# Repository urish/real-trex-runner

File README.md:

# In-Real-Life TRex Runner

## Documentation

- [About The Project + Hardware Guide](https://medium.com/@urish/i-saw-a-dinosaur-or-how-i-built-a-real-life-version-of-chrome-t-rex-game-92175f6cad2c)
- [Software Guide](https://www.javascriptjanuary.com/blog/irl-offline-t-rex-game-powered-by-javascript)

## License

[CC-BY-SA](https://creativecommons.org/licenses/by-sa/4.0/)

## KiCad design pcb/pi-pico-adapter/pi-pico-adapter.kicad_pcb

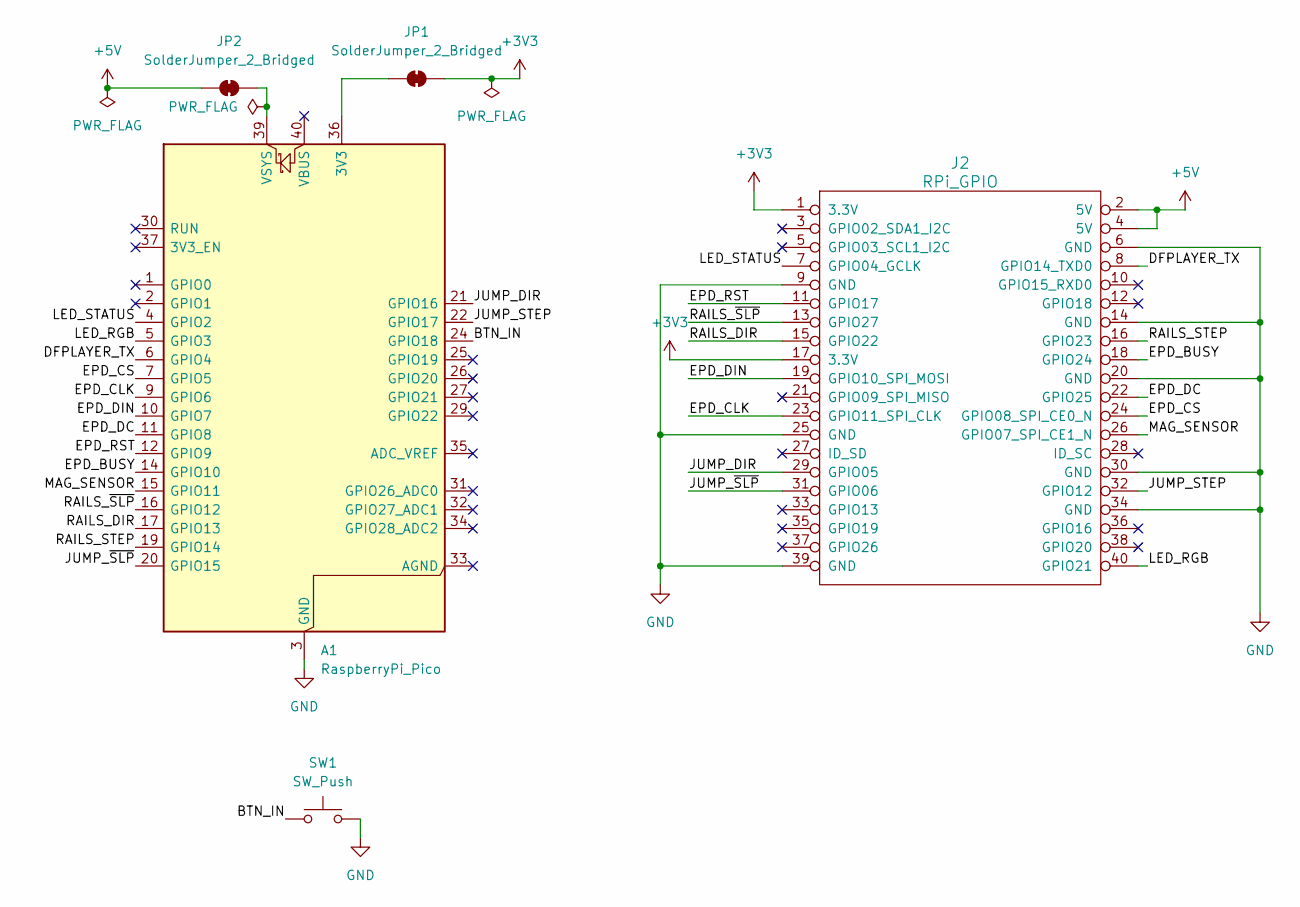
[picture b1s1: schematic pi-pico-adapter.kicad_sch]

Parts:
A1: RaspberryPi_Pico; RaspberryPi_Pico_Common_Unspecified
J2: RPi_GPIO; PinHeader_2x20_P2.54mm_Vertical
JP1, JP2: SolderJumper_2_Bridged; SolderJumper-2_P1.3mm_Bridged_RoundedPad1.0x1.5mm
SW1: SW_Push; PinHeader_1x02_P2.54mm_Vertical

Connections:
+3V3: J2.1 (3.3V), J2.17 (3.3V), JP1.2 (B)
+5V: J2.2 (5V), J2.4 (5V), JP2.1 (A)
/BTN_IN: A1.24 (GPIO18), SW1.1
/DFPLAYER_TX: A1.6 (GPIO4), J2.8 (GPIO14_TXD0)
/EPD_BUSY: A1.14 (GPIO10), J2.18 (GPIO24)
/EPD_CLK: A1.9 (GPIO6), J2.23 (GPIO11_SPI_CLK)
/EPD_CS: A1.7 (GPIO5), J2.24 (GPIO08_SPI_CE0_N)
/EPD_DC: A1.11 (GPIO8), J2.22 (GPIO25)
/EPD_DIN: A1.10 (GPIO7), J2.19 (GPIO10_SPI_MOSI)
/EPD_RST: A1.12 (GPIO9), J2.11 (GPIO17)
/JUMP_DIR: A1.21 (GPIO16), J2.29 (GPIO05)
/JUMP_STEP: A1.22 (GPIO17), J2.32 (GPIO12)
/JUMP_~SLP: A1.20 (GPIO15), J2.31 (GPIO06)
/LED_RGB: A1.5 (GPIO3), J2.40 (GPIO21)
/LED_STATUS: A1.4 (GPIO2), J2.7 (GPIO04_GCLK)
/MAG_SENSOR: A1.15 (GPIO11), J2.26 (GPIO07_SPI_CE1_N)
/RAILS_DIR: A1.17 (GPIO13), J2.15 (GPIO22)
/RAILS_STEP: A1.19 (GPIO14), J2.16 (GPIO23)
/RAILS_~SLP: A1.16 (GPIO12), J2.13 (GPIO27)
GND: A1.3 (GND), A1.8 (GND), A1.13 (GND), A1.18 (GND), A1.23 (GND), A1.28 (GND), A1.38 (GND), J2.6 (GND), J2.9 (GND), J2.14 (GND), J2.20 (GND), J2.25 (GND), J2.30 (GND), J2.34 (GND), J2.39 (GND), SW1.2
unnamed: A1.36 (3V3), JP1.1 (A)
unnamed: A1.39 (VSYS), JP2.2 (B)

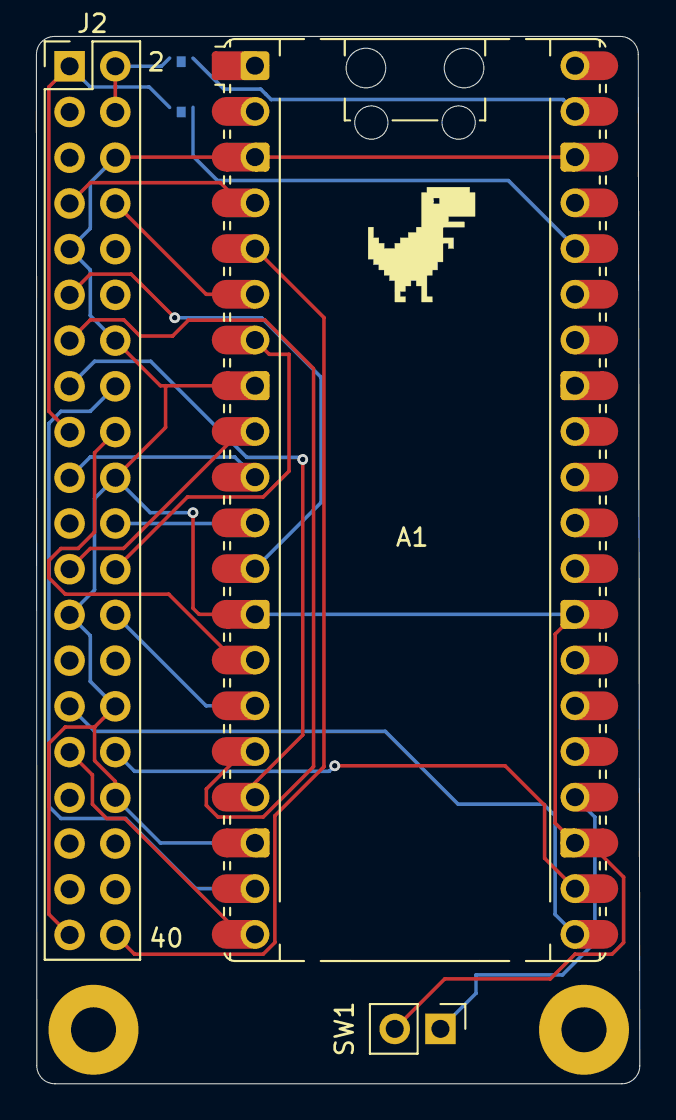
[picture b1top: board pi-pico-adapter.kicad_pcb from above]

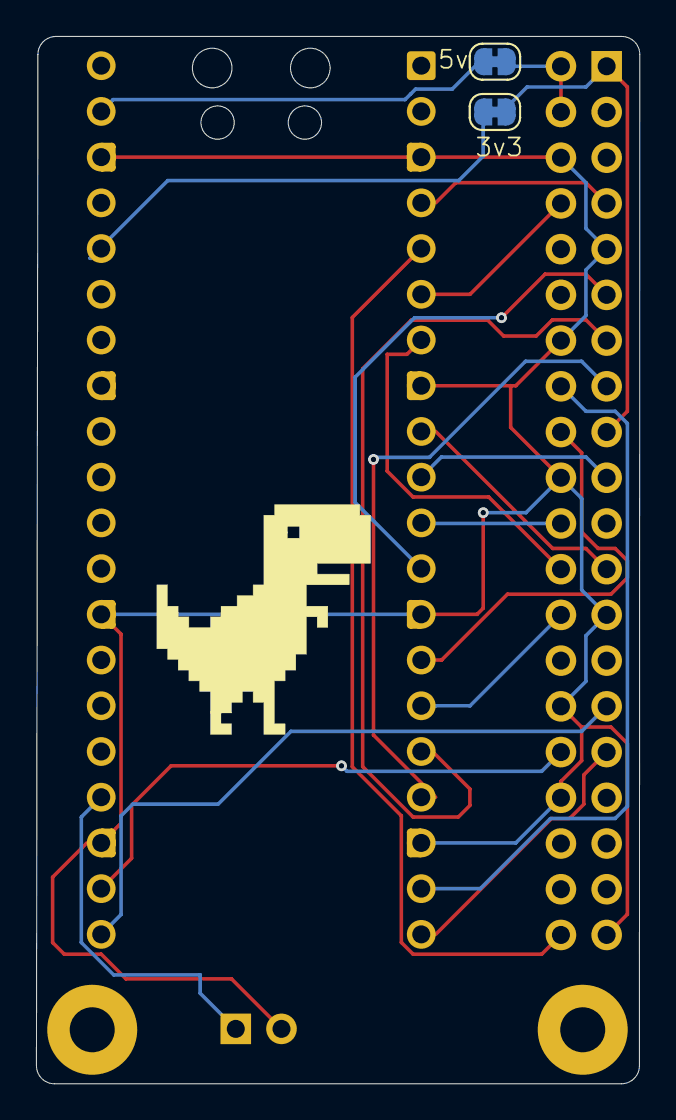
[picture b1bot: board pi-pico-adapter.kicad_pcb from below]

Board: 2 copper layers, 33.5 x 58.2 mm, 7 parts (3 on the bottom side), 22 nets.

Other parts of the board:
TREX1: trex
TREX2: trex-big

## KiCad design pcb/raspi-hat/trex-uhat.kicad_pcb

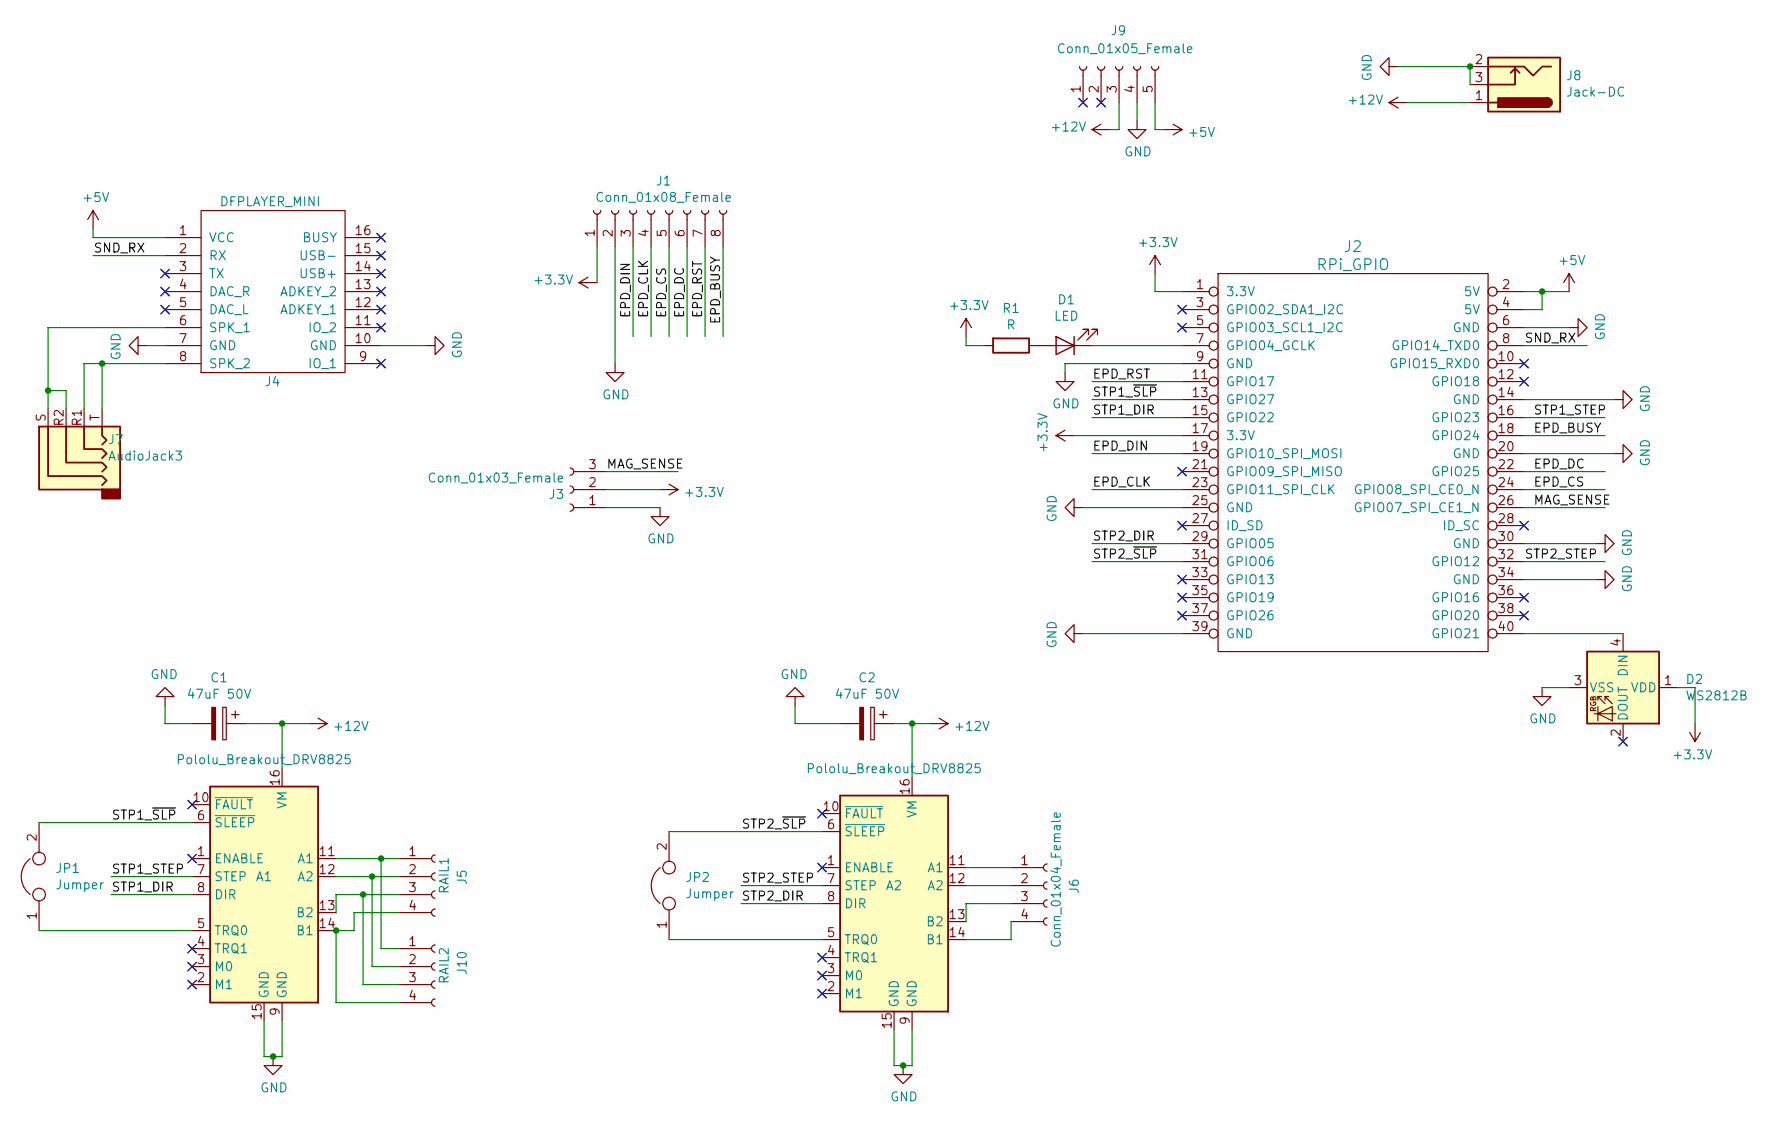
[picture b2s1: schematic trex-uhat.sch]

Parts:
A1, A2: Pololu_Breakout_DRV8825; Pololu_Breakout-16_15.2x20.3mm
C1, C2: 47uF 50V; CP_Radial_D6.3mm_P2.50mm
D1: LED; LED_D3.0mm
D2: WS2812B; LED_WS2812B_PLCC4_5.0x5.0mm_P3.2mm
J1: Conn_01x08_Female; PinSocket_1x08_P2.54mm_Vertical
J2: RPi_GPIO; PinSocket_2x20_P2.54mm_Vertical
J3: Conn_01x03_Female; PinSocket_1x03_P2.54mm_Vertical
J4: DFPLAYER_MINI; DFPlayer_Mini
J5: RAIL1; PinSocket_1x04_P2.54mm_Vertical
J6: Conn_01x04_Female; PinSocket_1x04_P2.54mm_Vertical
J7: AudioJack3; Jack_3.5mm_PJ320E_Horizontal
J8: Jack-DC; BarrelJack_CUI_PJ-102AH_Horizontal
J9: Conn_01x05_Female; PinSocket_1x05_P2.54mm_Vertical
J10: RAIL2; PinSocket_1x04_P2.54mm_Vertical
JP1, JP2: Jumper; SolderJumper-2_P1.3mm_Bridged_RoundedPad1.0x1.5mm
R1: R; R_1206_3216Metric

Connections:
+3V3: D2.1 (VDD), J1.1, J2.1 (3.3V), J2.17 (3.3V), J3.2, R1.2
+5V: J2.2 (5V), J2.4 (5V), J4.1 (VCC), J9.5
+12V: A1.16 (VM), A2.16 (VM), C1.1, C2.1, J8.1, J9.3
/EPD_BUSY: J1.8, J2.18 (GPIO24)
/EPD_CLK: J1.4, J2.23 (GPIO11_SPI_CLK)
/EPD_CS: J1.5, J2.24 (GPIO08_SPI_CE0_N)
/EPD_DC: J1.6, J2.22 (GPIO25)
/EPD_DIN: J1.3, J2.19 (GPIO10_SPI_MOSI)
/EPD_RST: J1.7, J2.11 (GPIO17)
/MAG_SENSE: J2.26 (GPIO07_SPI_CE1_N), J3.3
/SND_RX: J2.8 (GPIO14_TXD0), J4.2 (RX)
/STP1_DIR: A1.8 (DIR), J2.15 (GPIO22)
/STP1_STEP: A1.7 (STEP), J2.16 (GPIO23)
/STP1_~SLP: A1.6 (~SLEEP), J2.13 (GPIO27), JP1.2
/STP2_DIR: A2.8 (DIR), J2.29 (GPIO05)
/STP2_STEP: A2.7 (STEP), J2.32 (GPIO12)
/STP2_~SLP: A2.6 (~SLEEP), J2.31 (GPIO06), JP2.2
GND: A1.9 (GND), A1.15 (GND), A2.9 (GND), A2.15 (GND), C1.2, C2.2, D2.3 (VSS), J1.2, J2.6 (GND), J2.9 (GND), J2.14 (GND), J2.20 (GND), J2.25 (GND), J2.30 (GND), J2.34 (GND), J2.39 (GND), J3.1, J4.7 (GND), J4.10 (GND), J8.2, J8.3, J9.4
unnamed: A1.5 (TRQ0), JP1.1
unnamed: A1.11 (A1), J5.1, J10.1
unnamed: A1.12 (A2), J5.2, J10.2
unnamed: A1.13 (B2), J5.3, J10.3
unnamed: A1.14 (B1), J5.4, J10.4
unnamed: A2.5 (TRQ0), JP2.1
unnamed: A2.11 (A1), J6.1
unnamed: A2.12 (A2), J6.2
unnamed: A2.13 (B2), J6.3
unnamed: A2.14 (B1), J6.4
unnamed: D1.1 (K), J2.7 (GPIO04_GCLK)
unnamed: D1.2 (A), R1.1
unnamed: D2.4 (DIN), J2.40 (GPIO21)
unnamed: J4.6 (SPK_1), J7.R2, J7.S
unnamed: J4.8 (SPK_2), J7.R1, J7.T

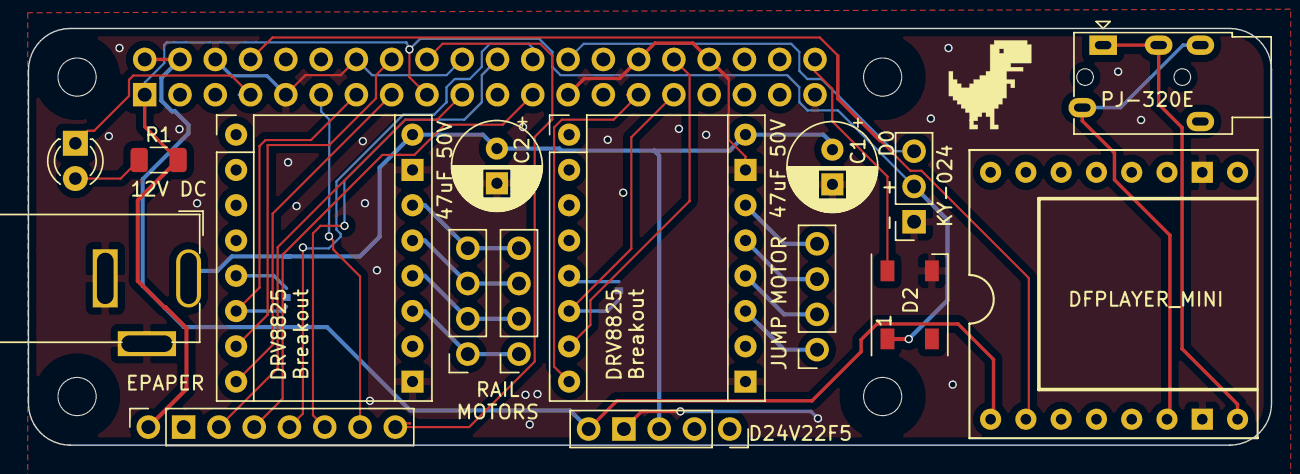
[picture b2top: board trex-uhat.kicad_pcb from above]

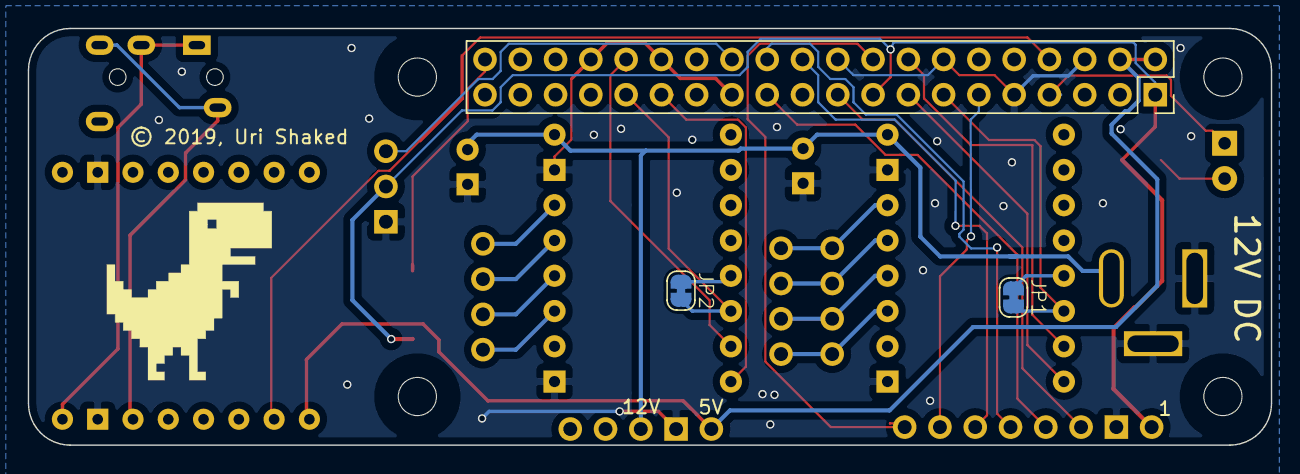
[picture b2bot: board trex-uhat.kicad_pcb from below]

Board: 2 copper layers, 89.5 x 30.0 mm, 21 parts (4 on the bottom side), 33 nets.

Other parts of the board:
TREX1: trex
TREX2: trex-big

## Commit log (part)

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2017-08-11 add cactus PCB
2017-09-29 feat: add js firmware code
2017-10-02 feat: add 3D-printed parts
2017-10-05 refactor: reorganize firmware directory
2017-10-05 feat: add display driver + unit tests
2017-10-05 feat(firmware): implement motor acceleration
2017-10-07 update DF Player pin, default speed
2017-10-07 fix: improve jump dynamics, fix name advertising
2017-10-07 refactor: move PCB files to `pcb` directory
2017-10-08 Implement scoring and game over mechanisms
2017-10-08 feat: add game sounds
2017-10-08 refactor: encode assets in base64 to save space
2017-10-08 fix: reset motor speed at the end of the game
2017-10-08 refactor: make display code asyncronous
2017-10-08 fix: remove artifacts from t-rex image
2017-10-08 refactor: move sound to separate module
2017-10-08 fix: reduce memory consumption of `fillMemory()`
2017-10-08 fix: improve cactus detection
2017-10-10 feat: potentimeter to control speed
2017-10-11 feat: add laser-cut walls and loop files
2017-10-12 add Loop Motor mounting part
2017-10-16 feat: add button cover model
2017-10-16 feat: add loop mount to bearing holder
2017-10-17 feat: wireless button, new jump mechanism
    replaced servo with a stepper for jumping
2017-10-17 fix: improve jump robustness, center text
2017-10-18 feat: additional 3D-printed parts
2017-10-18 feat: add front wall, t-bar laser cut files
2017-10-18 refactor: split bitmap assets into separate files
2017-10-18 feat: add background laser-cut file
2017-10-21 feat: add .editorconfig
2017-10-21 feat: initial version of the web page
2017-10-21 style: remove newline at the beginning of file
2017-10-21 fix: trim trailing '=' chars in encoded assets
2017-10-21 feat: implement high-score module
2017-10-21 fix(firmware): switch to soft PWM
2017-10-21 fix(firmware): throttle score updates
    also, don't try to update the display if it is busy
    this should probably fix most game glitches, especially when jumping
2017-10-22 fix: fix jump control code
    also disable the speed knob, it seems to mess up with the timings
2017-10-22 fix: improve magentic sensor code reliability
    also fix an issue with score display code
2017-10-22 fix: fine-tune jump
2017-10-22 fix: improve cactus detection accuracy
2017-10-22 feat: integrate highscore tracking
2017-10-22 fix: ignore cacti for the first 100ms of the game
    this prevents an immediate game-over sitaution
2017-10-22 feat: play level up sound every 10 points
2017-10-22 fix: reset lastCactusTime when game starts
2017-10-22 fix: level up sound did not play
2017-10-23 fix(web): change bg color to f7f7f7
2017-10-23 feat: improve end of game experience
2017-10-23 feat(web): read highscore from firebase
2017-10-23 feat(web): add TV page
2017-10-23 feat(web): update t-rex tv code
2017-10-23 fix: workaround for game over issue
2017-10-23 feat: update project page
2017-10-23 fix: reliability fixes
    disable the pot knob
    set default speed to 14k
    safety-net for speedup code
2017-10-23 fix(firmware): fix game getting stuck issue
2017-11-23 doc: update README
2018-06-29 feat: add latest Espruino firmware image
    also add build instructions
2018-06-30 feat(espruino): add new build, 1v99.95
2018-06-30 fix(firmware): disable cacti sensor when not playing
    otherwise we may end up stuck in an infinite loop of cacti events if the sensor was in an unstable state when the game stopped
2018-07-01 refactor(firmware): use Object Literal Shorthand syntax
2018-07-01 feat(firmware): display clock when no game is active
2018-07-28 fix: make dino go up at the beginning of game
2018-07-28 fix(firmware): make sure display is cleared correctly when starting a game
2018-08-01 feat(firmware): add DS3231 RTC module
2018-08-24 refactor(firmware): rewrite stepper control code in JS
    use nRF52 PPI hardware through NRF52LL to achieve accurate stepper motor control
2018-08-24 fix(firmware): change jump pin assignments
2018-08-24 feat: latest Espruino firmware
    - based on revision 000eadf6f8f637deb6090d55639a0f2246751d2c in
    Espruino master
    - add more memory (vars=2500 instead of 2250)
2019-08-21 fix(firmware): change default speed to 8k
2019-08-21 feat(firmware): implement button reconnect
2019-08-21 refactor(firmware): use Storage module for highscore
    https://www.espruino.com/Reference#t_Storage
2019-08-22 refactor(firmware): migrate assets to Storage
    use the Storage module to store assets instead of writing directly to Flash
2019-08-22 chore(firmware): upgrade rollup and plugins
2019-08-22 fix(firmware): improve jump
    also fix jump direction after hardware changes
2019-09-01 feat(pcb): Raspberry Pi ZeroW uHat PCB
    Design a uHat with all the game peripherals:
    - 2xDRV8880 Stepper Motor Driver
    - E-Paper Display connector
    - D24V22F5 5V Step-down regulator
    - KY-024 Magnetic sensor
    - 3mm LED
2019-09-01 fix(pcb): mirror DRV8880 breakout
    We want the potentiometer to be up
2019-09-02 fix(pcb): motor connections, replace audio + power jacks
    - Change power jack from PJ-063AH to the smaller PJ-102AH
    - Change audio jack from SJ1-3533NG to PJ320E
    - Fix motor connections: connect Pi to ~SLP instead of EN
    - Improve DFPlayer Mini Footprint
    - Add silk-screen texts
2019-09-23 feat(pcb): DRV8825 support
2019-09-23 refactor(firmware): migrate to raspberry pi
2019-09-24 refacotr(firmware): migrate display driver to pi
2019-09-24 cleanup(firmware): remove unused code
2019-09-24 refactor(firmware): migrate motor code to pi
2019-09-25 doc(firmware): add Pi setup instructions
2019-09-28 feat(firmware): implement cacti sensor driver
2019-09-28 fix(firmware): firm several glitches
    - display update timings
    - cacti sensor returing too much data
    - sound sometimes not playing
    - button registers multiple disconnect callbacks
    - highscore fails when files doesn't exist
2019-09-28 fix(firmware): improve button reconnect code
2019-12-11 chore(deps): bump extend from 3.0.1 to 3.0.2 in /firmware
    Bumps [extend](https://github.com/justmoon/node-extend) from 3.0.1 to 3.0.2.
    - [Release notes](https://github.com/justmoon/node-extend/releases)
    - [Changelog](https://github.com/justmoon/node-extend/blob/master/CHANGELOG.md)
    - [Commits](https://github.com/justmoon/node-extend/compare/v3.0.1...v3.0.2)
2019-12-11 chore(deps): bump lodash from 4.17.4 to 4.17.15 in /firmware
    Bumps [lodash](https://github.com/lodash/lodash) from 4.17.4 to 4.17.15.
    - [Release notes](https://github.com/lodash/lodash/releases)
    - [Commits](https://github.com/lodash/lodash/compare/4.17.4...4.17.15)
2019-12-11 chore(deps): bump merge from 1.2.0 to 1.2.1 in /firmware
    Bumps [merge](https://github.com/yeikos/js.merge) from 1.2.0 to 1.2.1.
    - [Release notes](https://github.com/yeikos/js.merge/releases)
    - [Commits](https://github.com/yeikos/js.merge/compare/v1.2.0...v1.2.1)
2019-12-11 chore(deps): bump diff from 3.3.1 to 3.5.0 in /firmware
    Bumps [diff](https://github.com/kpdecker/jsdiff) from 3.3.1 to 3.5.0.
    - [Release notes](https://github.com/kpdecker/jsdiff/releases)
    - [Changelog](https://github.com/kpdecker/jsdiff/blob/master/release-notes.md)
    - [Commits](https://github.com/kpdecker/jsdiff/compare/v3.3.1...v3.5.0)
2019-12-11 chore(deps): bump sshpk from 1.13.1 to 1.16.1 in /firmware
    Bumps [sshpk](https://github.com/joyent/node-sshpk) from 1.13.1 to 1.16.1.
    - [Release notes](https://github.com/joyent/node-sshpk/releases)
    - [Commits](https://github.com/joyent/node-sshpk/compare/v1.13.1...v1.16.1)
2019-12-11 chore(deps): bump fstream from 1.0.11 to 1.0.12 in /firmware
    Bumps [fstream](https://github.com/npm/fstream) from 1.0.11 to 1.0.12.
    - [Release notes](https://github.com/npm/fstream/releases)
    - [Commits](https://github.com/npm/fstream/compare/v1.0.11...v1.0.12)
2020-03-19 chore(firmware): create systemd service files
    Auto start trex firmware and pigpiod.
    Also update README with instructions.
2020-03-19 fix(firmware): write to display buffer line-by-line
    This aligns the code with WaveShare's example:
    https://github.com/waveshare/e-Paper/blob/8973995e53cb78bac6d1f8a66c2d398c18392f71/RaspberryPi%26JetsonNano/python/lib/waveshare_epd/epd2in9.py#L179
    It fixes display issues for larger buffers (e.g. full screen images)
2020-07-17 chore(deps): bump lodash from 4.17.15 to 4.17.19 in /firmware
    Bumps [lodash](https://github.com/lodash/lodash) from 4.17.15 to 4.17.19.
    - [Release notes](https://github.com/lodash/lodash/releases)
    - [Commits](https://github.com/lodash/lodash/compare/4.17.15...4.17.19)
2020-12-11 chore(deps): bump ini from 1.3.4 to 1.3.7 in /firmware
    Bumps [ini](https://github.com/isaacs/ini) from 1.3.4 to 1.3.7.
    - [Release notes](https://github.com/isaacs/ini/releases)
    - [Commits](https://github.com/isaacs/ini/compare/v1.3.4...v1.3.7)
2021-03-30 chore(deps): bump y18n from 3.2.1 to 3.2.2 in /firmware
    Bumps [y18n](https://github.com/yargs/y18n) from 3.2.1 to 3.2.2.
    - [Release notes](https://github.com/yargs/y18n/releases)
    - [Changelog](https://github.com/yargs/y18n/blob/master/CHANGELOG.md)
    - [Commits](https://github.com/yargs/y18n/commits)
2021-05-07 chore(deps): bump handlebars from 4.5.3 to 4.7.7 in /firmware
    Bumps [handlebars](https://github.com/wycats/handlebars.js) from 4.5.3 to 4.7.7.
    - [Release notes](https://github.com/wycats/handlebars.js/releases)
    - [Changelog](https://github.com/handlebars-lang/handlebars.js/blob/master/release-notes.md)
    - [Commits](https://github.com/wycats/handlebars.js/compare/v4.5.3...v4.7.7)
2021-05-10 chore(deps): bump hosted-git-info from 2.5.0 to 2.8.9 in /firmware
    Bumps [hosted-git-info](https://github.com/npm/hosted-git-info) from 2.5.0 to 2.8.9.
    - [Release notes](https://github.com/npm/hosted-git-info/releases)
    - [Changelog](https://github.com/npm/hosted-git-info/blob/v2.8.9/CHANGELOG.md)
    - [Commits](https://github.com/npm/hosted-git-info/compare/v2.5.0...v2.8.9)
2021-05-10 chore(deps): bump ini from 1.3.4 to 1.3.8 in /firmware
    Bumps [ini](https://github.com/isaacs/ini) from 1.3.4 to 1.3.8.
    - [Release notes](https://github.com/isaacs/ini/releases)
    - [Commits](https://github.com/isaacs/ini/compare/v1.3.4...v1.3.8)
2021-08-04 chore(deps): bump tar from 2.2.1 to 2.2.2 in /firmware
    Bumps [tar](https://github.com/npm/node-tar) from 2.2.1 to 2.2.2.
    - [Release notes](https://github.com/npm/node-tar/releases)
    - [Changelog](https://github.com/npm/node-tar/blob/main/CHANGELOG.md)
    - [Commits](https://github.com/npm/node-tar/compare/v2.2.1...v2.2.2)
    ---
    updated-dependencies:
2021-09-21 chore(deps): bump tmpl from 1.0.4 to 1.0.5 in /firmware
    Bumps [tmpl](https://github.com/daaku/nodejs-tmpl) from 1.0.4 to 1.0.5.
    - [Release notes](https://github.com/daaku/nodejs-tmpl/releases)
    - [Commits](https://github.com/daaku/nodejs-tmpl/commits/v1.0.5)
    ---
    updated-dependencies:
    - dependency-name: tmpl
2022-03-28 chore(deps): upgrade spi-device
2022-03-28 chore(deps): bump simple-get from 3.1.0 to 3.1.1 in /firmware
    Bumps [simple-get](https://github.com/feross/simple-get) from 3.1.0 to 3.1.1.
    - [Release notes](https://github.com/feross/simple-get/releases)
    - [Commits](https://github.com/feross/simple-get/compare/v3.1.0...v3.1.1)
    ---
    updated-dependencies:
    - dependency-name: simple-get
2022-12-07 chore(deps): bump qs from 6.4.0 to 6.4.1 in /firmware
    Bumps [qs](https://github.com/ljharb/qs) from 6.4.0 to 6.4.1.
    - [Release notes](https://github.com/ljharb/qs/releases)
    - [Changelog](https://github.com/ljharb/qs/blob/main/CHANGELOG.md)
    - [Commits](https://github.com/ljharb/qs/compare/v6.4.0...v6.4.1)
    ---
    updated-dependencies:
2025-04-16 feat(pcb): TRex adapter PCB for Pi Pico
2025-04-16 feat(pcb): button input (GP18) and mounting holes

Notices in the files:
pcb/raspi-hat/trex-uhat.kicad_pcb:
© 2019, Uri Shaked
